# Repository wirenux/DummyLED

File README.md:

# DummyLED 🔴🟢🔵

**DummyLED** is a beginner-friendly PCB project designed to demonstrate basic circuit logic and tactile interaction. The board features three momentary buttons, each controlling a dedicated Red, Green, or Blue LED using a 5V power rail.

## Overview

The goal of this project is to create a physical interface where:

1. Pressing Button 1 lights up the Red LED.
2. Pressing Button 2 lights up the Green LED.
3. Pressing Button 3 lights up the Blue LED.

The circuit is designed for a 5V supply, providing enough voltage "headroom" to drive Green and Blue LEDs (which typically require $>3.0\text{V}$) at full brightness.

## Technical Specifications

**Circuit Logic**

The board uses a series configuration for each LED branch:

5V Rail -> Tactile Switch -> Current Limiting Resistor -> LED -> GND.

**Resistor Calculations**

To ensure consistent brightness across different colors, the following resistance values were calculated using Ohm's Law:

$$R = \frac{V_{source} - V_f}{I}$$

| Components | $V_f$ (Forward Voltage) | Resistor Value |
| :---------------: | :---------------: | :---------------: |
| **Red LED** | $~2.0V$ | **$220Ω$** |
| **Green LED** | $~3.2V$ | **$220Ω$** |
| **Blue LED** | $~3.2V$  | **$150Ω$** |

## Schematic & Layout

**Schematic**

**PCB Layout**

## License

This project is release under [MIT License](./LICENSE).

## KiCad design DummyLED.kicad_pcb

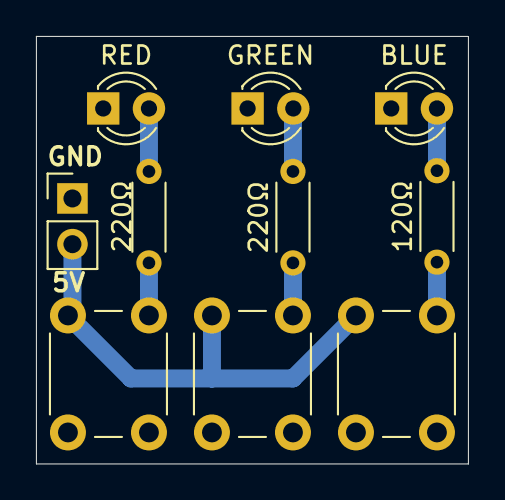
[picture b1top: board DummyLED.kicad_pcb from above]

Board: 2 copper layers, 24.0 x 23.8 mm, 10 parts (0 on the bottom side), 8 nets.

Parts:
120Ω, 220Ω: 120Ω; R_Axial_DIN0204_L3.6mm_D1.6mm_P5.08mm_Horizontal
220Ω#2: 220Ω; R_Axial_DIN0204_L3.6mm_D1.6mm_P5.08mm_Horizontal
BLUE: LED; LED_D3.0mm_FlatTop
GREEN: LED; LED_D3.0mm_FlatTop
J1: Conn_01x02; PinHeader_1x02_P2.54mm_Vertical
RED: LED; LED_D3.0mm_FlatTop
SW1, SW2, SW3: SW_DPST_x2; SW_PUSH_6mm

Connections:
+5V: J1.2, SW1.1 (A), SW2.1 (A), SW3.1 (A)
GND: BLUE.1 (K), GREEN.1 (K), J1.1, RED.1 (K)
unnamed: 220Ω#2.2, RED.2 (A)
unnamed: 220Ω.2, GREEN.2 (A)
unnamed: 120Ω.2, BLUE.2 (A)
unnamed: 220Ω#2.1, SW1.2 (B)
unnamed: 220Ω.1, SW2.2 (B)
unnamed: 120Ω.1, SW3.2 (B)

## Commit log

2026-05-11 init
2026-05-11 add: README.md + LICENSE
2026-05-11 add: Images/
2026-05-11 add: Images in README.md
